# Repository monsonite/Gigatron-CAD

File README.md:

# Gigatron-CAD
Eagle CAD Files for the Gigatron TTL Computer - Based on the design by Marcel van Kervinck

These files contain the Gigatron TTL computer schematics transcribed to Eagle CAD - using the IC numbers used in the original KiCAD.

For anyone wanting to build a machine based on the Gigatron design, the Eagle CAD schematic offers a known starting point.

Minor alterations have been made to allow easier routing specifically in the ALU section, where all 74HCT153 multiplexers use the same multiplexer section - and the logic constants into the other mux are the same for all devices.

There are both PDF and PNG overviews of the ALU and Memory sections - a convenient way of representing the complete design.

Certain components substitutions have been made for convenience of layout or saving space

74HCT273 has been exchanged for the more bus friendly 74HCT573

74HCT240 and 74HCT244 have been exchanged for 74F540 and 74F541 - again to give better bus flow.

The diode matrix in the control unit now uses SOT-23 dual common anode diodes to reduce space

If you want to make a very compact Gigatron using 74F series SMT packages, Eagle CAD allows all of the major IC packages to be easily swapped to their SMT equivalents

Gigatron has been run at between 12.5 and 15MHz using 74F series ICS

The 128K byte RAM expansion and additional 8-bit input and 8-bit output ports (for SPI) are also included in this version

Use the .sch files at your own risk - I cannot guarantee that they are completely error free.

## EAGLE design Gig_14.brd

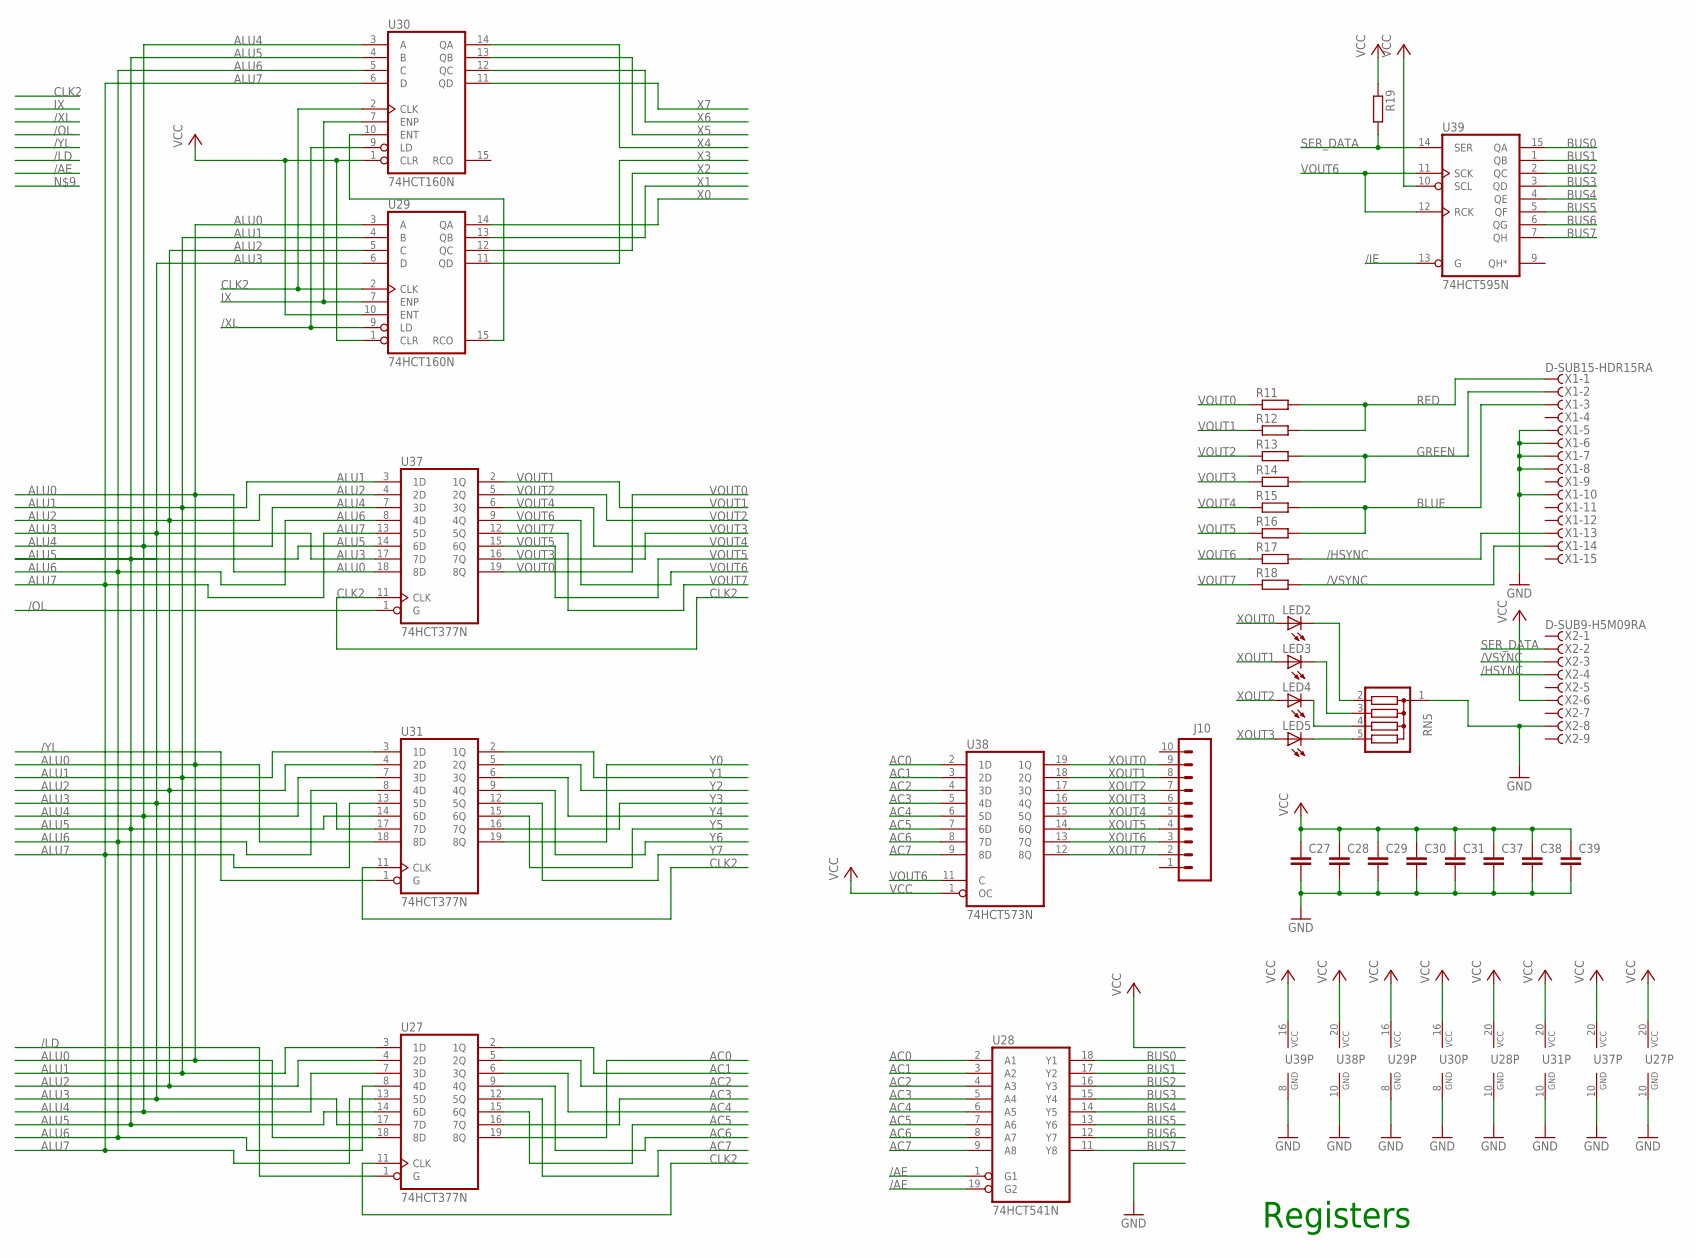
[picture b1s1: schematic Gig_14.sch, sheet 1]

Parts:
C27, C28, C29, C30, C31, C37, C38, C39: RCL_C-EU025-024X044; RCL_C025-024X044
J10: M10SILK_FEMALE_PTH; 1X10
LED2, LED3, LED4, LED5: LED3MM
R11, R12, R13, R14, R15, R16, R17, R18, R19: R-EU_0207/7; 0207/7
RN5: G04R; SIL5
U27, U31, U37: 74HCT377N; DIL20
U28: 74HCT541N; DIL20
U29, U30: 74HCT160N; DIL16
U38: 74HCT573N; DIL20
U39: 74HCT595N; DIL16
X1: D-SUB15-HDR15RA; HDR15RA
X2: D-SUB9-H5M09RA; H5M09RA

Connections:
/AE: U28.1 (G1), U28.19 (G2); also elsewhere on the board
/HSYNC: R17.2, X1.13, X2.4
/IE: U39.13 (G); also elsewhere on the board
/LD: U27.1 (G); also elsewhere on the board
/OL: U37.1 (G); also elsewhere on the board
/VSYNC: R18.2, X1.14, X2.3
/XL: U29.9 (LD), U30.9 (LD); also elsewhere on the board
/YL: U31.1 (G); also elsewhere on the board
AC0: U27.19 (8Q), U28.2 (A1), U38.2 (1D); also elsewhere on the board
AC1: U27.2 (1Q), U28.3 (A2), U38.3 (2D); also elsewhere on the board
AC2: U27.5 (2Q), U28.4 (A3), U38.4 (3D); also elsewhere on the board
AC3: U27.16 (7Q), U28.5 (A4), U38.5 (4D); also elsewhere on the board
AC4: U27.6 (3Q), U28.6 (A5), U38.6 (5D); also elsewhere on the board
AC5: U27.15 (6Q), U28.7 (A6), U38.7 (6D); also elsewhere on the board
AC6: U27.9 (4Q), U28.8 (A7), U38.8 (7D); also elsewhere on the board
AC7: U27.12 (5Q), U28.9 (A8), U38.9 (8D); also elsewhere on the board
ALU0: U27.18 (8D), U29.3 (A), U31.18 (8D), U37.18 (8D); also elsewhere on the board
ALU1: U27.3 (1D), U29.4 (B), U31.3 (1D), U37.3 (1D); also elsewhere on the board
ALU2: U27.4 (2D), U29.5 (C), U31.4 (2D), U37.4 (2D); also elsewhere on the board
ALU3: U27.17 (7D), U29.6 (D), U31.17 (7D), U37.17 (7D); also elsewhere on the board
ALU4: U27.7 (3D), U30.3 (A), U31.7 (3D), U37.7 (3D); also elsewhere on the board
ALU5: U27.14 (6D), U30.4 (B), U31.14 (6D), U37.14 (6D); also elsewhere on the board
ALU6: U27.8 (4D), U30.5 (C), U31.8 (4D), U37.8 (4D); also elsewhere on the board
ALU7: U27.13 (5D), U30.6 (D), U31.13 (5D), U37.13 (5D); also elsewhere on the board
BLUE: R15.2, R16.2, X1.3
BUS0: U28.18 (Y1), U39.15 (QA); also elsewhere on the board
BUS1: U28.17 (Y2), U39.1 (QB); also elsewhere on the board
BUS2: U28.16 (Y3), U39.2 (QC); also elsewhere on the board
BUS3: U28.15 (Y4), U39.3 (QD); also elsewhere on the board
BUS4: U28.14 (Y5), U39.4 (QE); also elsewhere on the board
BUS5: U28.13 (Y6), U39.5 (QF); also elsewhere on the board
BUS6: U28.12 (Y7), U39.6 (QG); also elsewhere on the board
BUS7: U28.11 (Y8), U39.7 (QH); also elsewhere on the board
CLK2: U27.11 (CLK), U29.2 (CLK), U30.2 (CLK), U31.11 (CLK), U37.11 (CLK); also elsewhere on the board
GND: C27.2, C28.2, C29.2, C30.2, C31.2, C37.2, C38.2, C39.2, RN5.1, U27.10 (GND), U28.10 (GND), U29.8 (GND), U30.8 (GND), U31.10 (GND), U37.10 (GND), U38.10 (GND), U39.8 (GND), X1.5, X1.6, X1.7, X1.8, X1.10, X2.8; also elsewhere on the board
GREEN: R13.2, R14.2, X1.2
IX: U29.7 (ENP), U30.7 (ENP); also elsewhere on the board
unnamed: U29.15 (RCO), U30.10 (ENT)
unnamed: LED2.K (C), RN5.2
unnamed: LED3.K (C), RN5.3
unnamed: LED4.K (C), RN5.4
unnamed: LED5.K (C), RN5.5
RED: R11.2, R12.2, X1.1
SER_DATA: R19.2, U39.14 (SER), X2.2
VCC: C27.1, C28.1, C29.1, C30.1, C31.1, C37.1, C38.1, C39.1, R19.1, U27.20 (VCC), U28.20 (VCC), U29.1 (CLR), U29.10 (ENT), U29.16 (VCC), U30.1 (CLR), U30.16 (VCC), U31.20 (VCC), U37.20 (VCC), U38.1 (OC), U38.20 (VCC), U39.10 (SCL), U39.16 (VCC), X2.6; also elsewhere on the board
VOUT0: R11.1, U37.19 (8Q)
VOUT1: R12.1, U37.2 (1Q)
VOUT2: R13.1, U37.5 (2Q)
VOUT3: R14.1, U37.16 (7Q)
VOUT4: R15.1, U37.6 (3Q)
VOUT5: R16.1, U37.15 (6Q)
VOUT6: R17.1, U37.9 (4Q), U38.11 (C), U39.11 (SCK), U39.12 (RCK)
VOUT7: R18.1, U37.12 (5Q)
X0: U29.14 (QA); also elsewhere on the board
X1: U29.13 (QB); also elsewhere on the board
X2: U29.12 (QC); also elsewhere on the board
X3: U29.11 (QD); also elsewhere on the board
X4: U30.14 (QA); also elsewhere on the board
X5: U30.13 (QB); also elsewhere on the board
X6: U30.12 (QC); also elsewhere on the board
X7: U30.11 (QD); also elsewhere on the board
XOUT0: J10.9, LED2.A, U38.19 (1Q)
XOUT1: J10.8, LED3.A, U38.18 (2Q)
XOUT2: J10.7, LED4.A, U38.17 (3Q)
XOUT3: J10.6, LED5.A, U38.16 (4Q)
XOUT4: J10.5, U38.15 (5Q)
XOUT5: J10.4, U38.14 (6Q)
XOUT6: J10.3, U38.13 (7Q)
XOUT7: J10.2, U38.12 (8Q)
Y0: U31.19 (8Q); also elsewhere on the board
Y1: U31.2 (1Q); also elsewhere on the board
Y2: U31.5 (2Q); also elsewhere on the board
Y3: U31.16 (7Q); also elsewhere on the board
Y4: U31.6 (3Q); also elsewhere on the board
Y5: U31.15 (6Q); also elsewhere on the board
Y6: U31.9 (4Q); also elsewhere on the board
Y7: U31.12 (5Q); also elsewhere on the board

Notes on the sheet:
Registers

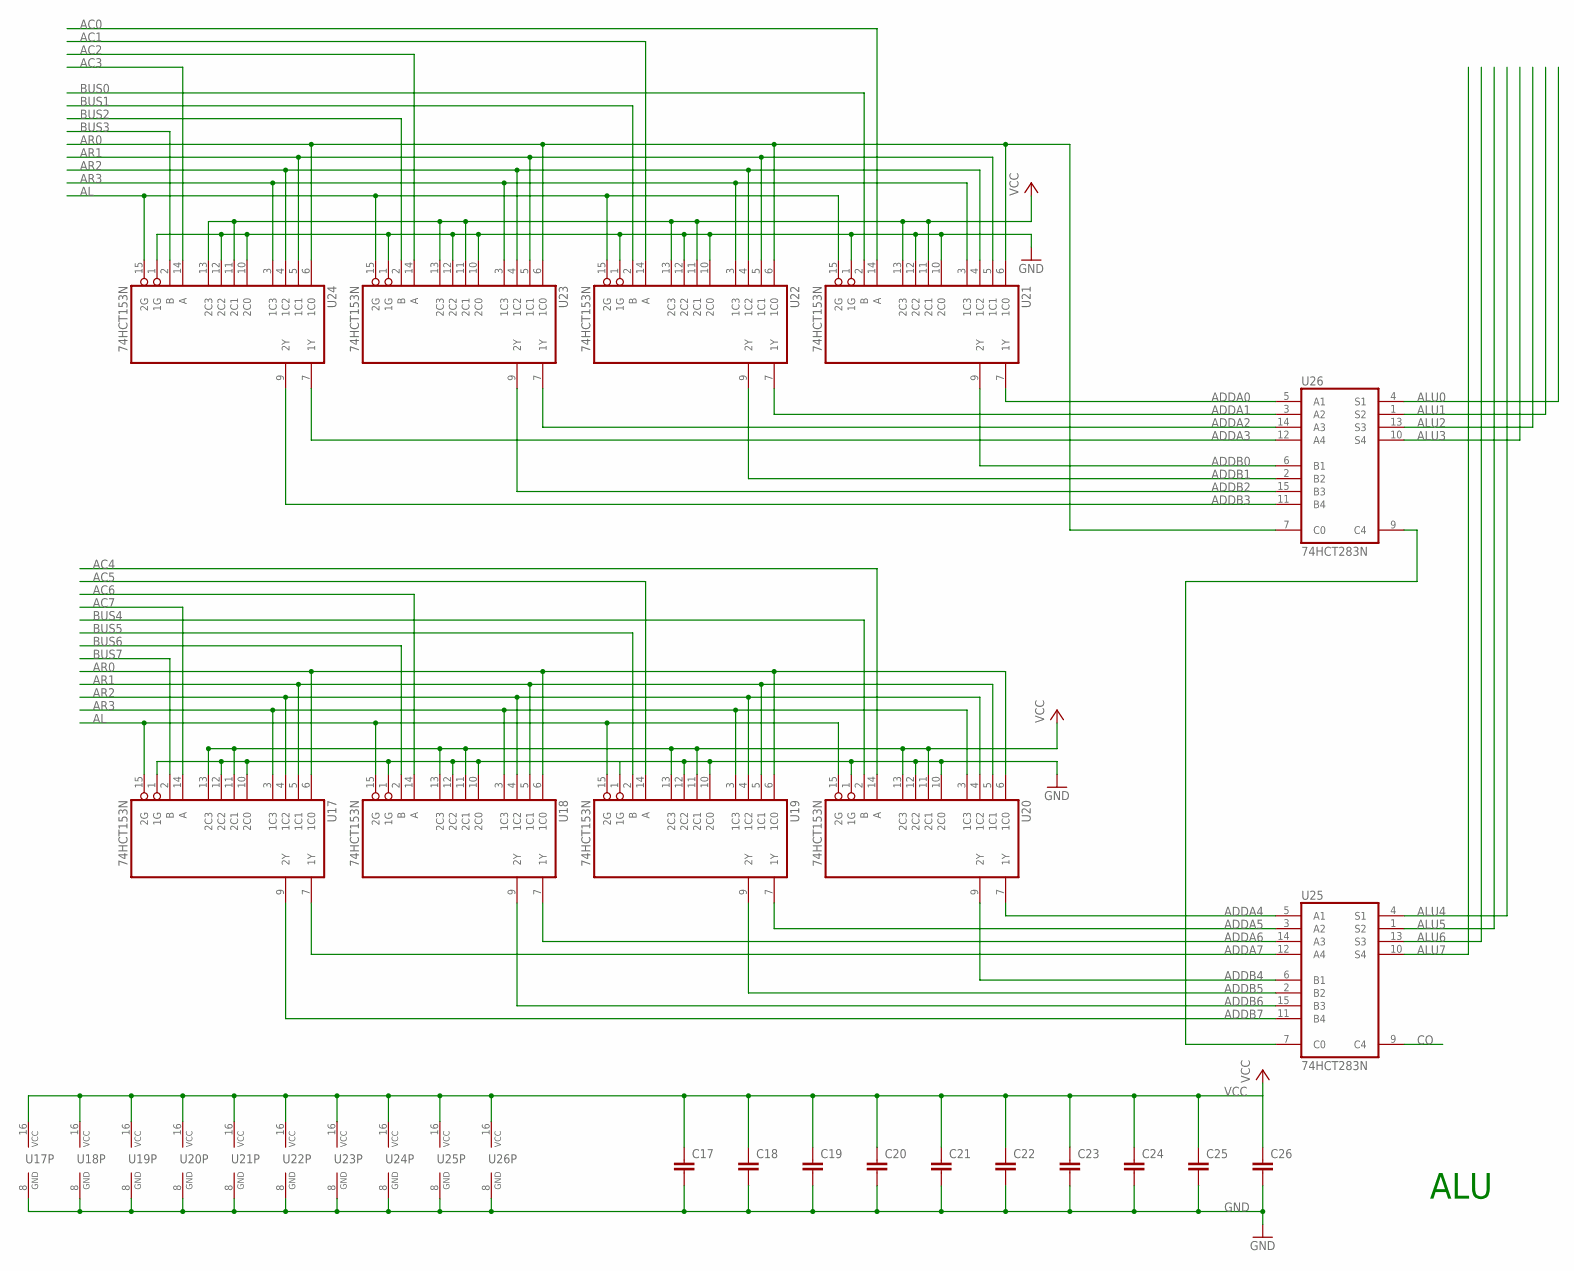
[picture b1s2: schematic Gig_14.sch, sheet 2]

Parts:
C17, C18, C19, C20, C21, C22, C23, C24, C25, C26: RCL_C-EU025-024X044; RCL_C025-024X044
U17, U18, U19, U20, U21, U22, U23, U24: 74HCT153N; DIL16
U25, U26: 74HCT283N; DIL16

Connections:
AC0: U21.14 (A); also elsewhere on the board
AC1: U22.14 (A); also elsewhere on the board
AC2: U23.14 (A); also elsewhere on the board
AC3: U24.14 (A); also elsewhere on the board
AC4: U20.14 (A); also elsewhere on the board
AC5: U19.14 (A); also elsewhere on the board
AC6: U18.14 (A); also elsewhere on the board
AC7: U17.14 (A); also elsewhere on the board
ADDA0: U21.7 (1Y), U26.5 (A1)
ADDA1: U22.7 (1Y), U26.3 (A2)
ADDA2: U23.7 (1Y), U26.14 (A3)
ADDA3: U24.7 (1Y), U26.12 (A4)
ADDA4: U20.7 (1Y), U25.5 (A1)
ADDA5: U19.7 (1Y), U25.3 (A2)
ADDA6: U18.7 (1Y), U25.14 (A3)
ADDA7: U17.7 (1Y), U25.12 (A4)
ADDB0: U21.9 (2Y), U26.6 (B1)
ADDB1: U22.9 (2Y), U26.2 (B2)
ADDB2: U23.9 (2Y), U26.15 (B3)
ADDB3: U24.9 (2Y), U26.11 (B4)
ADDB4: U20.9 (2Y), U25.6 (B1)
ADDB5: U19.9 (2Y), U25.2 (B2)
ADDB6: U18.9 (2Y), U25.15 (B3)
ADDB7: U17.9 (2Y), U25.11 (B4)
AL: U17.15 (2G), U18.15 (2G), U19.15 (2G), U20.15 (2G), U21.15 (2G), U22.15 (2G), U23.15 (2G), U24.15 (2G); also elsewhere on the board
ALU0: U26.4 (S1); also elsewhere on the board
ALU1: U26.1 (S2); also elsewhere on the board
ALU2: U26.13 (S3); also elsewhere on the board
ALU3: U26.10 (S4); also elsewhere on the board
ALU4: U25.4 (S1); also elsewhere on the board
ALU5: U25.1 (S2); also elsewhere on the board
ALU6: U25.13 (S3); also elsewhere on the board
ALU7: U25.10 (S4); also elsewhere on the board
AR0: U17.6 (1C0), U18.6 (1C0), U19.6 (1C0), U20.6 (1C0), U21.6 (1C0), U22.6 (1C0), U23.6 (1C0), U24.6 (1C0), U26.7 (C0); also elsewhere on the board
AR1: U17.5 (1C1), U18.5 (1C1), U19.5 (1C1), U20.5 (1C1), U21.5 (1C1), U22.5 (1C1), U23.5 (1C1), U24.5 (1C1); also elsewhere on the board
AR2: U17.4 (1C2), U18.4 (1C2), U19.4 (1C2), U20.4 (1C2), U21.4 (1C2), U22.4 (1C2), U23.4 (1C2), U24.4 (1C2); also elsewhere on the board
AR3: U17.3 (1C3), U18.3 (1C3), U19.3 (1C3), U20.3 (1C3), U21.3 (1C3), U22.3 (1C3), U23.3 (1C3), U24.3 (1C3); also elsewhere on the board
BUS0: U21.2 (B); also elsewhere on the board
BUS1: U22.2 (B); also elsewhere on the board
BUS2: U23.2 (B); also elsewhere on the board
BUS3: U24.2 (B); also elsewhere on the board
BUS4: U20.2 (B); also elsewhere on the board
BUS5: U19.2 (B); also elsewhere on the board
BUS6: U18.2 (B); also elsewhere on the board
BUS7: U17.2 (B); also elsewhere on the board
CO: U25.9 (C4); also elsewhere on the board
GND: C17.2, C18.2, C19.2, C20.2, C21.2, C22.2, C23.2, C24.2, C25.2, C26.2, U17.1 (1G), U17.8 (GND), U17.10 (2C0), U17.12 (2C2), U18.1 (1G), U18.8 (GND), U18.10 (2C0), U18.12 (2C2), U19.1 (1G), U19.8 (GND), U19.10 (2C0), U19.12 (2C2), U20.1 (1G), U20.8 (GND), U20.10 (2C0), U20.12 (2C2), U21.1 (1G), U21.8 (GND), U21.10 (2C0), U21.12 (2C2), U22.1 (1G), U22.8 (GND), U22.10 (2C0), U22.12 (2C2), U23.1 (1G), U23.8 (GND), U23.10 (2C0), U23.12 (2C2), U24.1 (1G), U24.8 (GND), U24.10 (2C0), U24.12 (2C2), U25.8 (GND), U26.8 (GND); also elsewhere on the board
unnamed: U25.7 (C0), U26.9 (C4)
VCC: C17.1, C18.1, C19.1, C20.1, C21.1, C22.1, C23.1, C24.1, C25.1, C26.1, U17.11 (2C1), U17.13 (2C3), U17.16 (VCC), U18.11 (2C1), U18.13 (2C3), U18.16 (VCC), U19.11 (2C1), U19.13 (2C3), U19.16 (VCC), U20.11 (2C1), U20.13 (2C3), U20.16 (VCC), U21.11 (2C1), U21.13 (2C3), U21.16 (VCC), U22.11 (2C1), U22.13 (2C3), U22.16 (VCC), U23.11 (2C1), U23.13 (2C3), U23.16 (VCC), U24.11 (2C1), U24.13 (2C3), U24.16 (VCC), U25.16 (VCC), U26.16 (VCC); also elsewhere on the board

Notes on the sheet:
ALU

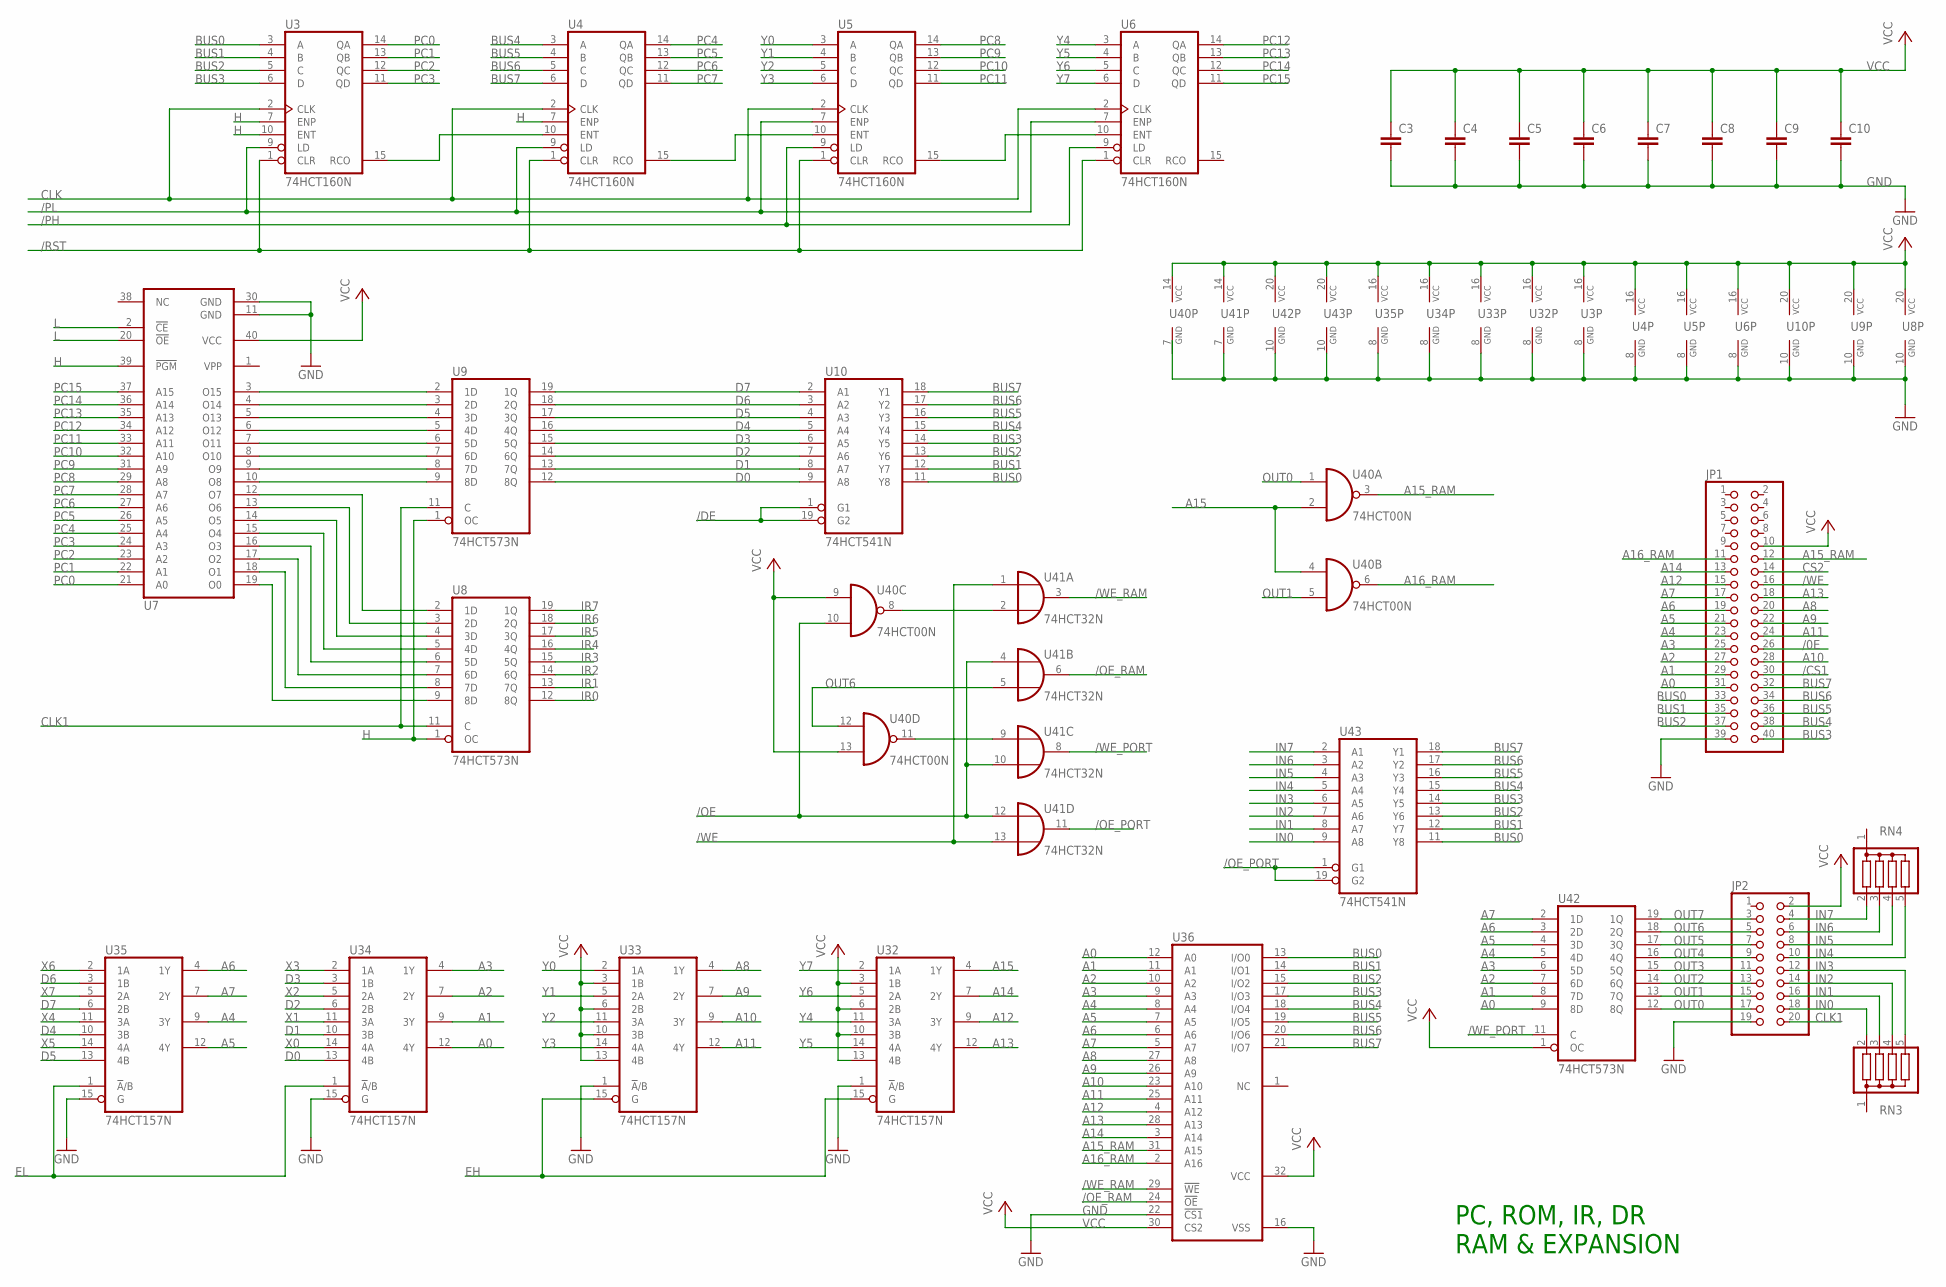
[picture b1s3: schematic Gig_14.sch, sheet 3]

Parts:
C3, C4, C5, C6, C7, C8, C9, C10: RCL_C-EU025-024X044; RCL_C025-024X044
JP1: PINHD-2X20; 2X20
JP2: PINHD-2X10; 2X10
RN3, RN4: G04R; SIL5
U3, U4, U5, U6: 74HCT160N; DIL16
U7: 27C1024D; DIL40
U8, U9, U42: 74HCT573N; DIL20
U10, U43: 74HCT541N; DIL20
U32, U33, U34, U35: 74HCT157N; DIL16
U36: 628128P; DIL32
U40: 74HCT00N; DIL14
U41: 74HCT32N; DIL14

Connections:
/0E: JP1.26
/CS1: JP1.30
/DE: U10.1 (G1), U10.19 (G2); also elsewhere on the board
/OE: U40.10 (I1), U41.4 (I0), U41.10 (I1), U41.12 (I0); also elsewhere on the board
/OE_PORT: U41.11 (O), U43.1 (G1), U43.19 (G2)
/OE_RAM: U36.24 (!OE), U41.6 (O)
/PH: U5.9 (LD), U6.9 (LD); also elsewhere on the board
/PL: U3.9 (LD), U4.9 (LD), U5.7 (ENP), U6.7 (ENP); also elsewhere on the board
/RST: U3.1 (CLR), U4.1 (CLR), U5.1 (CLR), U6.1 (CLR); also elsewhere on the board
/WE: JP1.16, U41.1 (I0), U41.13 (I1); also elsewhere on the board
/WE_PORT: U41.8 (O), U42.11 (C)
/WE_RAM: U36.29 (!WE), U41.3 (O)
A0: JP1.31, U34.12 (4Y), U36.12 (A0), U42.9 (8D)
A1: JP1.29, U34.9 (3Y), U36.11 (A1), U42.8 (7D)
A2: JP1.27, U34.7 (2Y), U36.10 (A2), U42.7 (6D)
A3: JP1.25, U34.4 (1Y), U36.9 (A3), U42.6 (5D)
A4: JP1.23, U35.9 (3Y), U36.8 (A4), U42.5 (4D)
A5: JP1.21, U35.12 (4Y), U36.7 (A5), U42.4 (3D)
A6: JP1.19, U35.4 (1Y), U36.6 (A6), U42.3 (2D)
A7: JP1.17, U35.7 (2Y), U36.5 (A7), U42.2 (1D)
A8: JP1.20, U33.4 (1Y), U36.27 (A8)
A9: JP1.22, U33.7 (2Y), U36.26 (A9)
A10: JP1.28, U33.9 (3Y), U36.23 (A10)
A11: JP1.24, U33.12 (4Y), U36.25 (A11)
A12: JP1.15, U32.9 (3Y), U36.4 (A12)
A13: JP1.18, U32.12 (4Y), U36.28 (A13)
A14: JP1.13, U32.7 (2Y), U36.3 (A14)
A15: U32.4 (1Y), U40.2 (I1), U40.4 (I0)
A15_RAM: JP1.12, U36.31 (A15), U40.3 (O)
A16_RAM: JP1.11, U36.2 (A16), U40.6 (O)
BUS0: JP1.33, U3.3 (A), U10.11 (Y8), U36.13 (I/O0), U43.11 (Y8); also elsewhere on the board
BUS1: JP1.35, U3.4 (B), U10.12 (Y7), U36.14 (I/O1), U43.12 (Y7); also elsewhere on the board
BUS2: JP1.37, U3.5 (C), U10.13 (Y6), U36.15 (I/O2), U43.13 (Y6); also elsewhere on the board
BUS3: JP1.40, U3.6 (D), U10.14 (Y5), U36.17 (I/O3), U43.14 (Y5); also elsewhere on the board
BUS4: JP1.38, U4.3 (A), U10.15 (Y4), U36.18 (I/O4), U43.15 (Y4); also elsewhere on the board
BUS5: JP1.36, U4.4 (B), U10.16 (Y3), U36.19 (I/O5), U43.16 (Y3); also elsewhere on the board
BUS6: JP1.34, U4.5 (C), U10.17 (Y2), U36.20 (I/O6), U43.17 (Y2); also elsewhere on the board
BUS7: JP1.32, U4.6 (D), U10.18 (Y1), U36.21 (I/O7), U43.18 (Y1); also elsewhere on the board
CLK: U3.2 (CLK), U4.2 (CLK), U5.2 (CLK), U6.2 (CLK)
CLK1: JP2.20, U8.11 (C), U9.11 (C); also elsewhere on the board
CS2: JP1.14
D0: U9.12 (8Q), U10.9 (A8), U34.13 (4B)
D1: U9.13 (7Q), U10.8 (A7), U34.10 (3B)
D2: U9.14 (6Q), U10.7 (A6), U34.6 (2B)
D3: U9.15 (5Q), U10.6 (A5), U34.3 (1B)
D4: U9.16 (4Q), U10.5 (A4), U35.10 (3B)
D5: U9.17 (3Q), U10.4 (A3), U35.13 (4B)
D6: U9.18 (2Q), U10.3 (A2), U35.3 (1B)
D7: U9.19 (1Q), U10.2 (A1), U35.6 (2B)
EH: U32.15 (G), U33.15 (G); also elsewhere on the board
EL: U34.1 (!A!/B), U35.1 (!A!/B); also elsewhere on the board
GND: C3.2, C4.2, C5.2, C6.2, C7.2, C8.2, C9.2, C10.2, JP1.39, JP2.19, U3.8 (GND), U4.8 (GND), U5.8 (GND), U6.8 (GND), U7.11 (GND), U7.30 (GND), U8.10 (GND), U9.10 (GND), U10.10 (GND), U32.1 (!A!/B), U32.8 (GND), U33.1 (!A!/B), U33.8 (GND), U34.8 (GND), U34.15 (G), U35.8 (GND), U35.15 (G), U36.16 (VSS), U36.22 (!CS1), U40.7 (GND), U41.7 (GND), U42.10 (GND), U43.10 (GND); also elsewhere on the board
H: U3.7 (ENP), U3.10 (ENT), U4.7 (ENP), U7.39 (!PGM), U8.1 (OC), U9.1 (OC)
IN0: JP2.18, RN3.2, U43.9 (A8)
IN1: JP2.16, RN3.3, U43.8 (A7)
IN2: JP2.14, RN3.4, U43.7 (A6)
IN3: JP2.12, RN3.5, U43.6 (A5)
IN4: JP2.10, RN4.5, U43.5 (A4)
IN5: JP2.8, RN4.4, U43.4 (A3)
IN6: JP2.6, RN4.3, U43.3 (A2)
IN7: JP2.4, RN4.2, U43.2 (A1)
IR0: U8.12 (8Q); also elsewhere on the board
IR1: U8.13 (7Q); also elsewhere on the board
IR2: U8.14 (6Q); also elsewhere on the board
IR3: U8.15 (5Q); also elsewhere on the board
IR4: U8.16 (4Q); also elsewhere on the board
IR5: U8.17 (3Q); also elsewhere on the board
IR6: U8.18 (2Q); also elsewhere on the board
IR7: U8.19 (1Q); also elsewhere on the board
L: U7.2 (!CE), U7.20 (!OE)
unnamed: U40.8 (O), U41.2 (I1)
unnamed: U40.11 (O), U41.9 (I0)
unnamed: U7.3 (O15), U9.2 (1D)
unnamed: U7.4 (O14), U9.3 (2D)
unnamed: U7.5 (O13), U9.4 (3D)
unnamed: U7.6 (O12), U9.5 (4D)
unnamed: U7.7 (O11), U9.6 (5D)
unnamed: U7.8 (O10), U9.7 (6D)
unnamed: U7.9 (O9), U9.8 (7D)
unnamed: U7.10 (O8), U9.9 (8D)
unnamed: U7.12 (O7), U8.2 (1D)
unnamed: U7.13 (O6), U8.3 (2D)
unnamed: U7.14 (O5), U8.4 (3D)
unnamed: U7.15 (O4), U8.5 (4D)
unnamed: U7.16 (O3), U8.6 (5D)
unnamed: U7.17 (O2), U8.7 (6D)
unnamed: U7.18 (O1), U8.8 (7D)
unnamed: U7.19 (O0), U8.9 (8D)
unnamed: U3.15 (RCO), U4.10 (ENT)
unnamed: U4.15 (RCO), U5.10 (ENT)
unnamed: U5.15 (RCO), U6.10 (ENT)
OUT0: JP2.17, U40.1 (I0), U42.12 (8Q)
OUT1: JP2.15, U40.5 (I1), U42.13 (7Q)
OUT2: JP2.13, U42.14 (6Q)
OUT3: JP2.11, U42.15 (5Q)
OUT4: JP2.9, U42.16 (4Q)
OUT5: JP2.7, U42.17 (3Q)
OUT6: JP2.5, U40.12 (I0), U41.5 (I1), U42.18 (2Q)
OUT7: JP2.3, U42.19 (1Q)
PC0: U3.14 (QA), U7.21 (A0)
PC1: U3.13 (QB), U7.22 (A1)
PC2: U3.12 (QC), U7.23 (A2)
PC3: U3.11 (QD), U7.24 (A3)
PC4: U4.14 (QA), U7.25 (A4)
PC5: U4.13 (QB), U7.26 (A5)
PC6: U4.12 (QC), U7.27 (A6)
PC7: U4.11 (QD), U7.28 (A7)
PC8: U5.14 (QA), U7.29 (A8)
PC9: U5.13 (QB), U7.31 (A9)
PC10: U5.12 (QC), U7.32 (A10)
PC11: U5.11 (QD), U7.33 (A11)
PC12: U6.14 (QA), U7.34 (A12)
PC13: U6.13 (QB), U7.35 (A13)
PC14: U6.12 (QC), U7.36 (A14)
PC15: U6.11 (QD), U7.37 (A15)
VCC: C3.1, C4.1, C5.1, C6.1, C7.1, C8.1, C9.1, C10.1, JP1.10, JP2.2, U3.16 (VCC), U4.16 (VCC), U5.16 (VCC), U6.16 (VCC), U7.40 (VCC), U8.20 (VCC), U9.20 (VCC), U10.20 (VCC), U32.3 (1B), U32.6 (2B), U32.10 (3B), U32.13 (4B), U32.16 (VCC), U33.3 (1B), U33.6 (2B), U33.10 (3B), U33.13 (4B), U33.16 (VCC), U34.16 (VCC), U35.16 (VCC), U36.30 (CS2), U36.32 (VCC), U40.9 (I0), U40.13 (I1), U40.14 (VCC), U41.14 (VCC), U42.1 (OC), U42.20 (VCC), U43.20 (VCC); also elsewhere on the board
X0: U34.14 (4A); also elsewhere on the board
X1: U34.11 (3A); also elsewhere on the board
X2: U34.5 (2A); also elsewhere on the board
X3: U34.2 (1A); also elsewhere on the board
X4: U35.11 (3A); also elsewhere on the board
X5: U35.14 (4A); also elsewhere on the board
X6: U35.2 (1A); also elsewhere on the board
X7: U35.5 (2A); also elsewhere on the board
Y0: U5.3 (A), U33.2 (1A); also elsewhere on the board
Y1: U5.4 (B), U33.5 (2A); also elsewhere on the board
Y2: U5.5 (C), U33.11 (3A); also elsewhere on the board
Y3: U5.6 (D), U33.14 (4A); also elsewhere on the board
Y4: U6.3 (A), U32.11 (3A); also elsewhere on the board
Y5: U6.4 (B), U32.14 (4A); also elsewhere on the board
Y6: U6.5 (C), U32.5 (2A); also elsewhere on the board
Y7: U6.6 (D), U32.2 (1A); also elsewhere on the board

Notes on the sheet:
PC, ROM, IR, DR RAM & EXPANSION

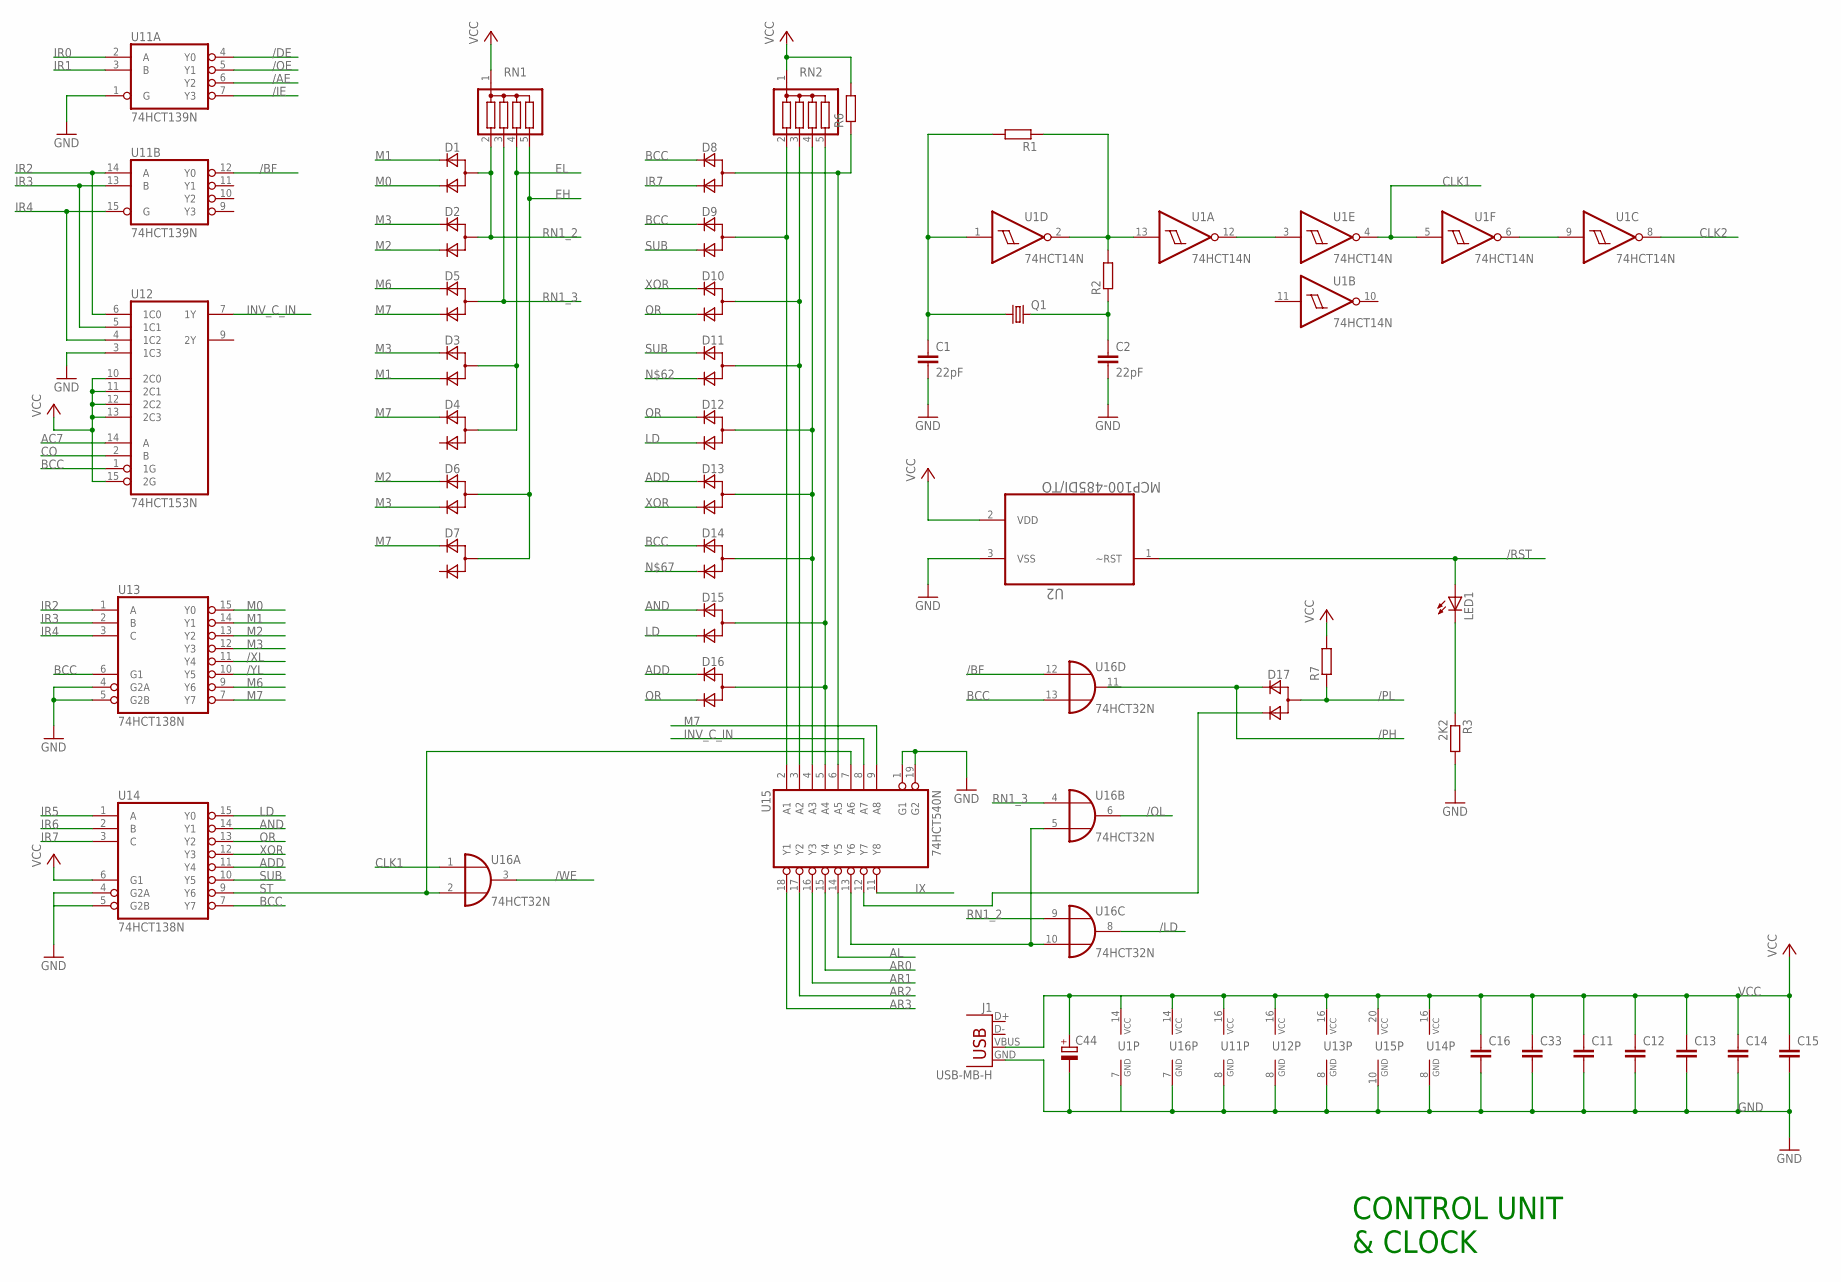
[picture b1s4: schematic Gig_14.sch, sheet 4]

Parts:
C1, C2: 22pF; RCL_C025-024X044
C11, C12, C13, C14, C15, C16, C33: RCL_C-EU025-024X044; RCL_C025-024X044
C44: CPOL-EUE5-8.5; E5-8,5
D1, D2, D3, D4, D5, D6, D7, D8, D9, D10, D11, D12, D13, D14, D15, D16, D17: D_2CSOT23; SOT-23
J1: USB-MB-H
LED1: LED_LED3MM
Q1: CRYSTALHC49S; HC49/S
R1, R2, R7: R-EU_0207/7; 0207/7
R3: 2K2; 0207/7
R6: R-EU_0207/12; 0207/12
RN1, RN2: G04R; SIL5
U1: 74HCT14N; DIL14
U2: MCP100-485DI/TO; TO127P254X495-3
U11: 74HCT139N; DIL16
U12: 74HCT153N; DIL16
U13, U14: 74HCT138N; DIL16
U15: 74HCT540N; DIL20
U16: 74HCT32N; DIL14

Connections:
/AE: U11.6 (Y2); also elsewhere on the board
/BF: U11.12 (Y0), U16.12 (I0)
/DE: U11.4 (Y0); also elsewhere on the board
/IE: U11.7 (Y3); also elsewhere on the board
/LD: U16.8 (O); also elsewhere on the board
/OE: U11.5 (Y1); also elsewhere on the board
/OL: U16.6 (O); also elsewhere on the board
/PH: D17.2 (C1); also elsewhere on the board
/PL: D17.1 (A), R7.1; also elsewhere on the board
/RST: LED1.A, U2.1 (~RST); also elsewhere on the board
/WE: U16.3 (O); also elsewhere on the board
/XL: U13.11 (Y4); also elsewhere on the board
/YL: U13.10 (Y5); also elsewhere on the board
AC7: U12.14 (A); also elsewhere on the board
ADD: D13.2 (C1), D16.2 (C1), U14.11 (Y4)
AL: U15.14 (Y5); also elsewhere on the board
AND: D15.2 (C1), U14.14 (Y1)
AR0: U15.15 (Y4); also elsewhere on the board
AR1: U15.16 (Y3); also elsewhere on the board
AR2: U15.17 (Y2); also elsewhere on the board
AR3: U15.18 (Y1); also elsewhere on the board
BCC: D8.2 (C1), D9.2 (C1), D14.2 (C1), U12.1 (1G), U13.6 (G1), U14.7 (Y7), U16.13 (I1)
CLK1: U1.4 (O), U1.5 (I), U16.1 (I0); also elsewhere on the board
CLK2: U1.8 (O); also elsewhere on the board
CO: U12.2 (B); also elsewhere on the board
EH: D6.1 (A), D7.1 (A), RN1.5; also elsewhere on the board
EL: D3.1 (A), D4.1 (A), RN1.4; also elsewhere on the board
GND: C1.2, C2.2, C11.2, C12.2, C13.2, C14.2, C15.2, C16.2, C33.2, C44.-, J1.GND, R3.2, U1.7 (GND), U2.3 (VSS), U11.1 (G), U11.8 (GND), U12.3 (1C3), U12.8 (GND), U13.4 (G2A), U13.5 (G2B), U13.8 (GND), U14.4 (G2A), U14.5 (G2B), U14.8 (GND), U15.1 (G1), U15.10 (GND), U15.19 (G2), U16.7 (GND); also elsewhere on the board
INV_C_IN: U12.7 (1Y), U15.8 (A7)
IR0: U11.2 (A); also elsewhere on the board
IR1: U11.3 (B); also elsewhere on the board
IR2: U11.14 (A), U12.6 (1C0), U13.1 (A); also elsewhere on the board
IR3: U11.13 (B), U12.5 (1C1), U13.2 (B); also elsewhere on the board
IR4: U11.15 (G), U12.4 (1C2), U13.3 (C); also elsewhere on the board
IR5: U14.1 (A); also elsewhere on the board
IR6: U14.2 (B); also elsewhere on the board
IR7: D8.3 (C2), U14.3 (C); also elsewhere on the board
IX: U15.11 (Y8); also elsewhere on the board
LD: D12.3 (C2), D15.3 (C2), U14.15 (Y0)
M0: D1.3 (C2), U13.15 (Y0)
M1: D1.2 (C1), D3.3 (C2), U13.14 (Y1)
M2: D2.3 (C2), D6.2 (C1), U13.13 (Y2)
M3: D2.2 (C1), D3.2 (C1), D6.3 (C2), U13.12 (Y3)
M6: D5.2 (C1), U13.9 (Y6)
M7: D4.2 (C1), D5.3 (C2), D7.2 (C1), U13.7 (Y7), U15.9 (A8)
unnamed: D8.1 (A), R6.1, U15.6 (A5)
unnamed: C1.1, Q1.1, R1.2, U1.1 (I)
unnamed: D17.3 (C2), U15.12 (Y7)
unnamed: C2.1, Q1.2, R2.1
unnamed: R1.1, R2.2, U1.2 (O), U1.13 (I)
unnamed: D9.1 (A), RN2.2, U15.2 (A1)
unnamed: D10.1 (A), D11.1 (A), RN2.3, U15.3 (A2)
unnamed: D12.1 (A), D13.1 (A), D14.1 (A), RN2.4, U15.4 (A3)
unnamed: D15.1 (A), D16.1 (A), RN2.5, U15.5 (A4)
unnamed: U1.3 (I), U1.12 (O)
unnamed: U15.13 (Y6), U16.5 (I1), U16.10 (I1)
unnamed: LED1.K (C), R3.1
unnamed: U1.6 (O), U1.9 (I)
OR: D10.3 (C2), D12.2 (C1), D16.3 (C2), U14.13 (Y2)
RN1_2: D1.1 (A), D2.1 (A), RN1.2, U16.9 (I0)
RN1_3: D5.1 (A), RN1.3, U16.4 (I0)
ST: U14.9 (Y6), U15.7 (A6), U16.2 (I1)
SUB: D9.3 (C2), D11.2 (C1), U14.10 (Y5)
VCC: C11.1, C12.1, C13.1, C14.1, C15.1, C16.1, C33.1, C44.+, J1.VBUS, R6.2, R7.2, RN1.1, RN2.1, U1.14 (VCC), U2.2 (VDD), U11.16 (VCC), U12.10 (2C0), U12.11 (2C1), U12.12 (2C2), U12.13 (2C3), U12.15 (2G), U12.16 (VCC), U13.16 (VCC), U14.6 (G1), U14.16 (VCC), U15.20 (VCC), U16.14 (VCC); also elsewhere on the board
XOR: D10.2 (C1), D13.3 (C2), U14.12 (Y3)

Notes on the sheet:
CONTROL UNIT & CLOCK

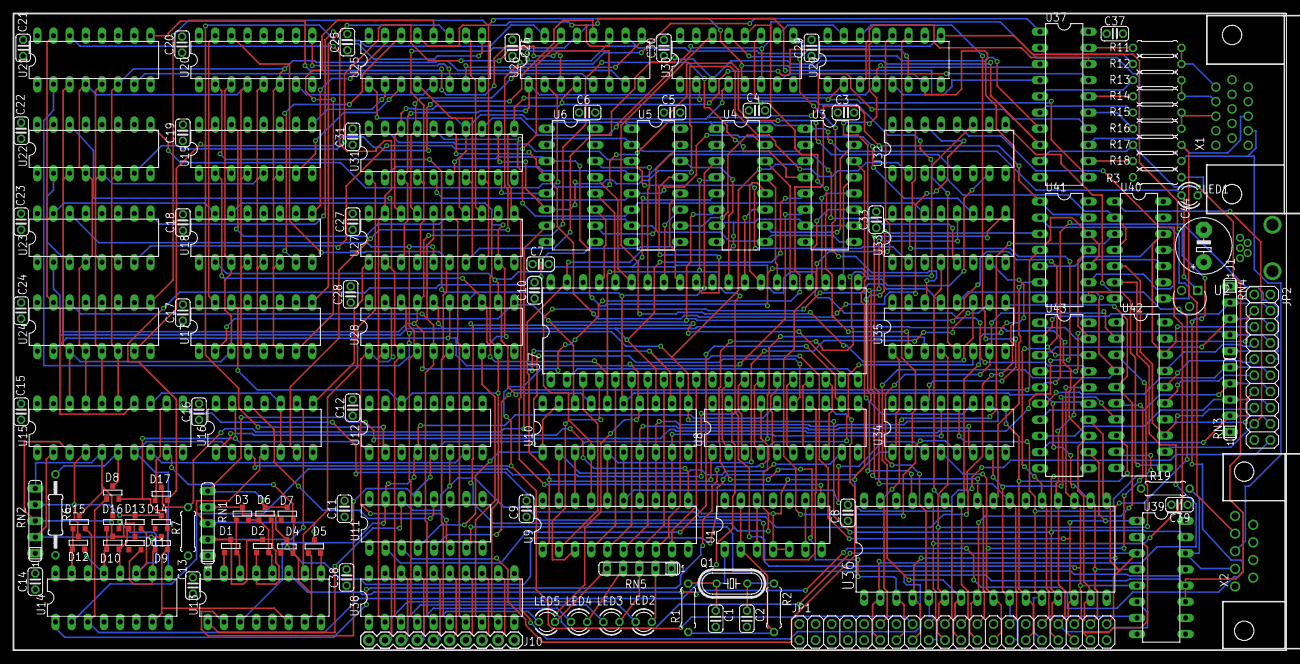
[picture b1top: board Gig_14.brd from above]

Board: 4 copper layers, 199.9 x 100.0 mm, 127 parts (0 on the bottom side), 234 nets.

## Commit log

2019-05-05 Add files via upload
    Gigatron TTL Computer Eagle CAD (v6.60) files

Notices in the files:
parts and their libraries:
SparkFun-Connectors: Licensing: Creative Commons ShareAlike 4.0 International - https://creativecommons.org/licenses/by-sa/4.0
